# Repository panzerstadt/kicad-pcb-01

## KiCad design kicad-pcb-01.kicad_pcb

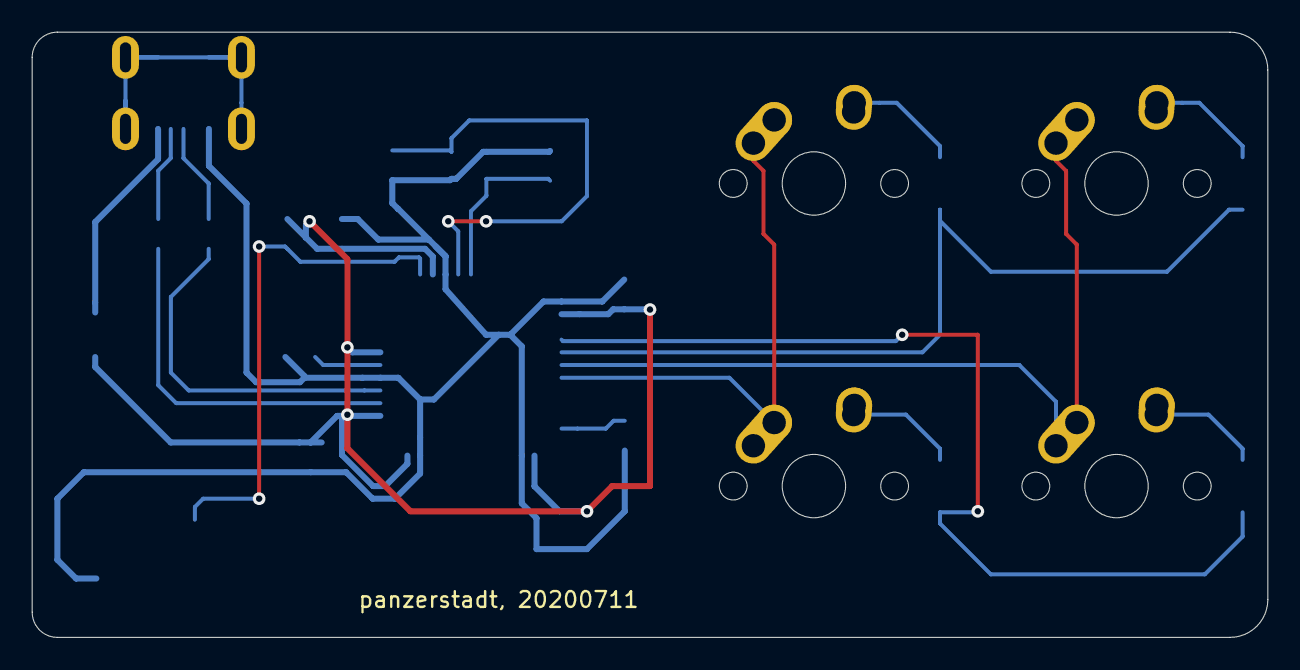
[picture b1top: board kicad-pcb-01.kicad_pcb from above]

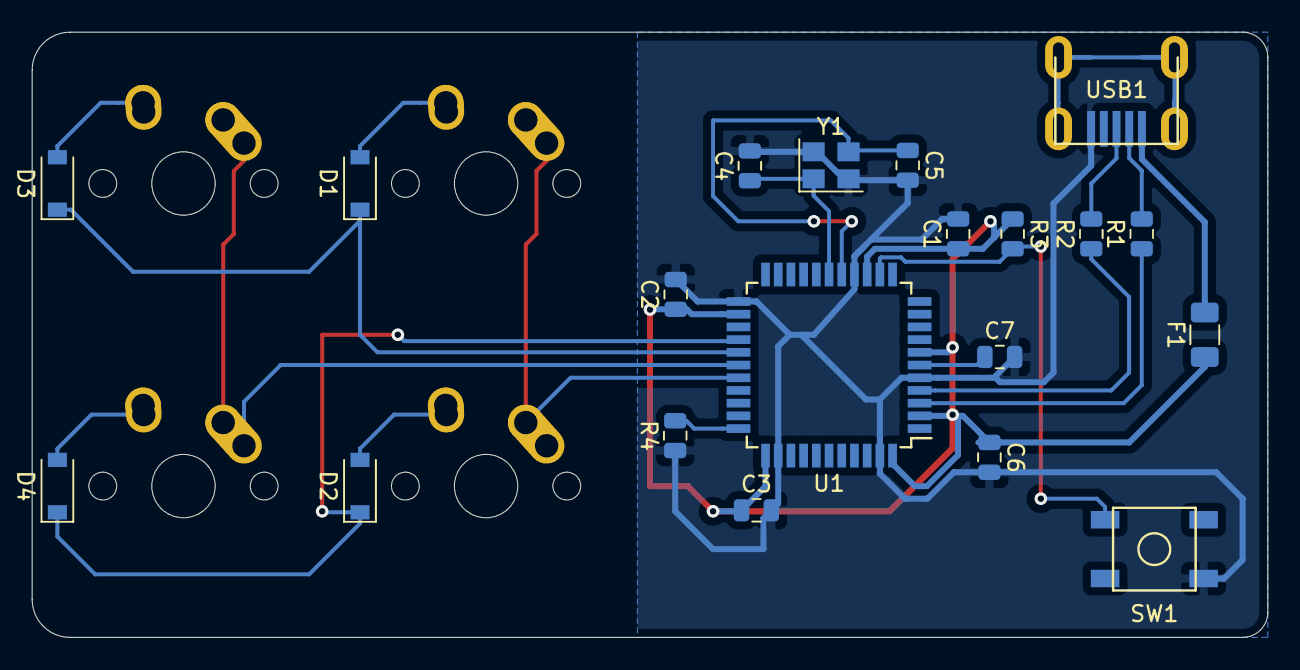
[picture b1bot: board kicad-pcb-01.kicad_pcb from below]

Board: 2 copper layers, 77.8 x 38.1 mm, 24 parts (20 on the bottom side), 20 nets.

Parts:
C1, C2, C3: 0.1uF; C_0805_2012Metric
C4, C5: 22pF; C_0805_2012Metric
C6: 10uF; C_0805_2012Metric
C7: 1uF; C_0805_2012Metric
D1, D2, D3, D4: SOD-123; D_SOD-123
F1: 500mA; Fuse_1206_3216Metric
MX1, MX2, MX3, MX4: MX-NoLED; MX-1U-NoLED
R1, R2: 22; R_0805_2012Metric
R3, R4: 10k; R_0805_2012Metric
SW1: SW_Push; SKQG-1155865
U1: ATmega32U4-AU; TQFP-44_10x10mm_P0.8mm
USB1: Molex-0548190589
Y1: 16MHz; Crystal_SMD_3225-4Pin_3.2x2.5mm

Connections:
+5V: C1.1, C2.1, C3.1, C6.1, F1.1, R3.1, U1.2, U1.7, U1.14, U1.24, U1.34, U1.44
COL0: MX1.1, MX2.1, U1.29
COL1: MX3.1, MX4.1, U1.28
D+: R2.2, USB1.3
D-: R1.2, USB1.4
GND: C1.2, C2.2, C3.2, C4.2, C5.2, C6.2, C7.2, R4.1, SW1.1, U1.5, U1.15, U1.23, U1.35, U1.43, USB1.1, Y1.2, Y1.4
unnamed: C4.1, U1.17, Y1.1
unnamed: C5.1, U1.16, Y1.3
unnamed: C7.1, U1.6
unnamed: D1.2, MX1.2
unnamed: D2.2, MX2.2
unnamed: D3.2, MX3.2
unnamed: D4.2, MX4.2
unnamed: R1.1, U1.3
unnamed: R2.1, U1.4
unnamed: R3.2, SW1.2, U1.13
unnamed: R4.2, U1.33
ROW0: D1.1, D3.1, U1.27
ROW1: D2.1, D4.1, U1.26
VCC: F1.2, USB1.5

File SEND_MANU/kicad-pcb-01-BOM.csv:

Comment,Designator,Footprint,LCSC
"0.1uF","C1,C2,C3","Capacitor_SMD:C_0805_2012Metric","C1711"
"22pF","C4,C5","Capacitor_SMD:C_0805_2012Metric","C465168"
"10uF","C6","Capacitor_SMD:C_0805_2012Metric","C307520"
"1uF","C7","Capacitor_SMD:C_0805_2012Metric","C116352"
"SOD-123","D1,D2,D3,D4","Diode_SMD:D_SOD-123","C77978"
"500mA","F1","Fuse:Fuse_1206_3216Metric","C151162"
"22","R1,R2","Resistor_SMD:R_0805_2012Metric","C413152"
"10k","R3,R4","Resistor_SMD:R_0805_2012Metric","C191101"
"SW_Push","SW1","random-keyboard-parts:SKQG-1155865","C221929"
"ATmega32U4-AU","U1","Package_QFP:TQFP-44_10x10mm_P0.8mm","C44854"
"Molex-0548190589","USB1","random-keyboard-parts:Molex-0548190589","C105424"
"16MHz","Y1","Crystal:Crystal_SMD_3225-4Pin_3.2x2.5mm","C254367"

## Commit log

2020-05-27 init
2020-05-27 add submodules
2020-05-27 setup libs
2020-05-27 part 3 decoupling capacitors
2020-05-27 mcu ready part 3
2020-05-28 added usb and switches, labeled all pcb parts and mapped them to components
2020-06-25 pcb layout
2020-07-10 routing complete
2020-07-10 complete
2020-07-10 added lcsc part ref:
2020-07-10 lcsc parts
